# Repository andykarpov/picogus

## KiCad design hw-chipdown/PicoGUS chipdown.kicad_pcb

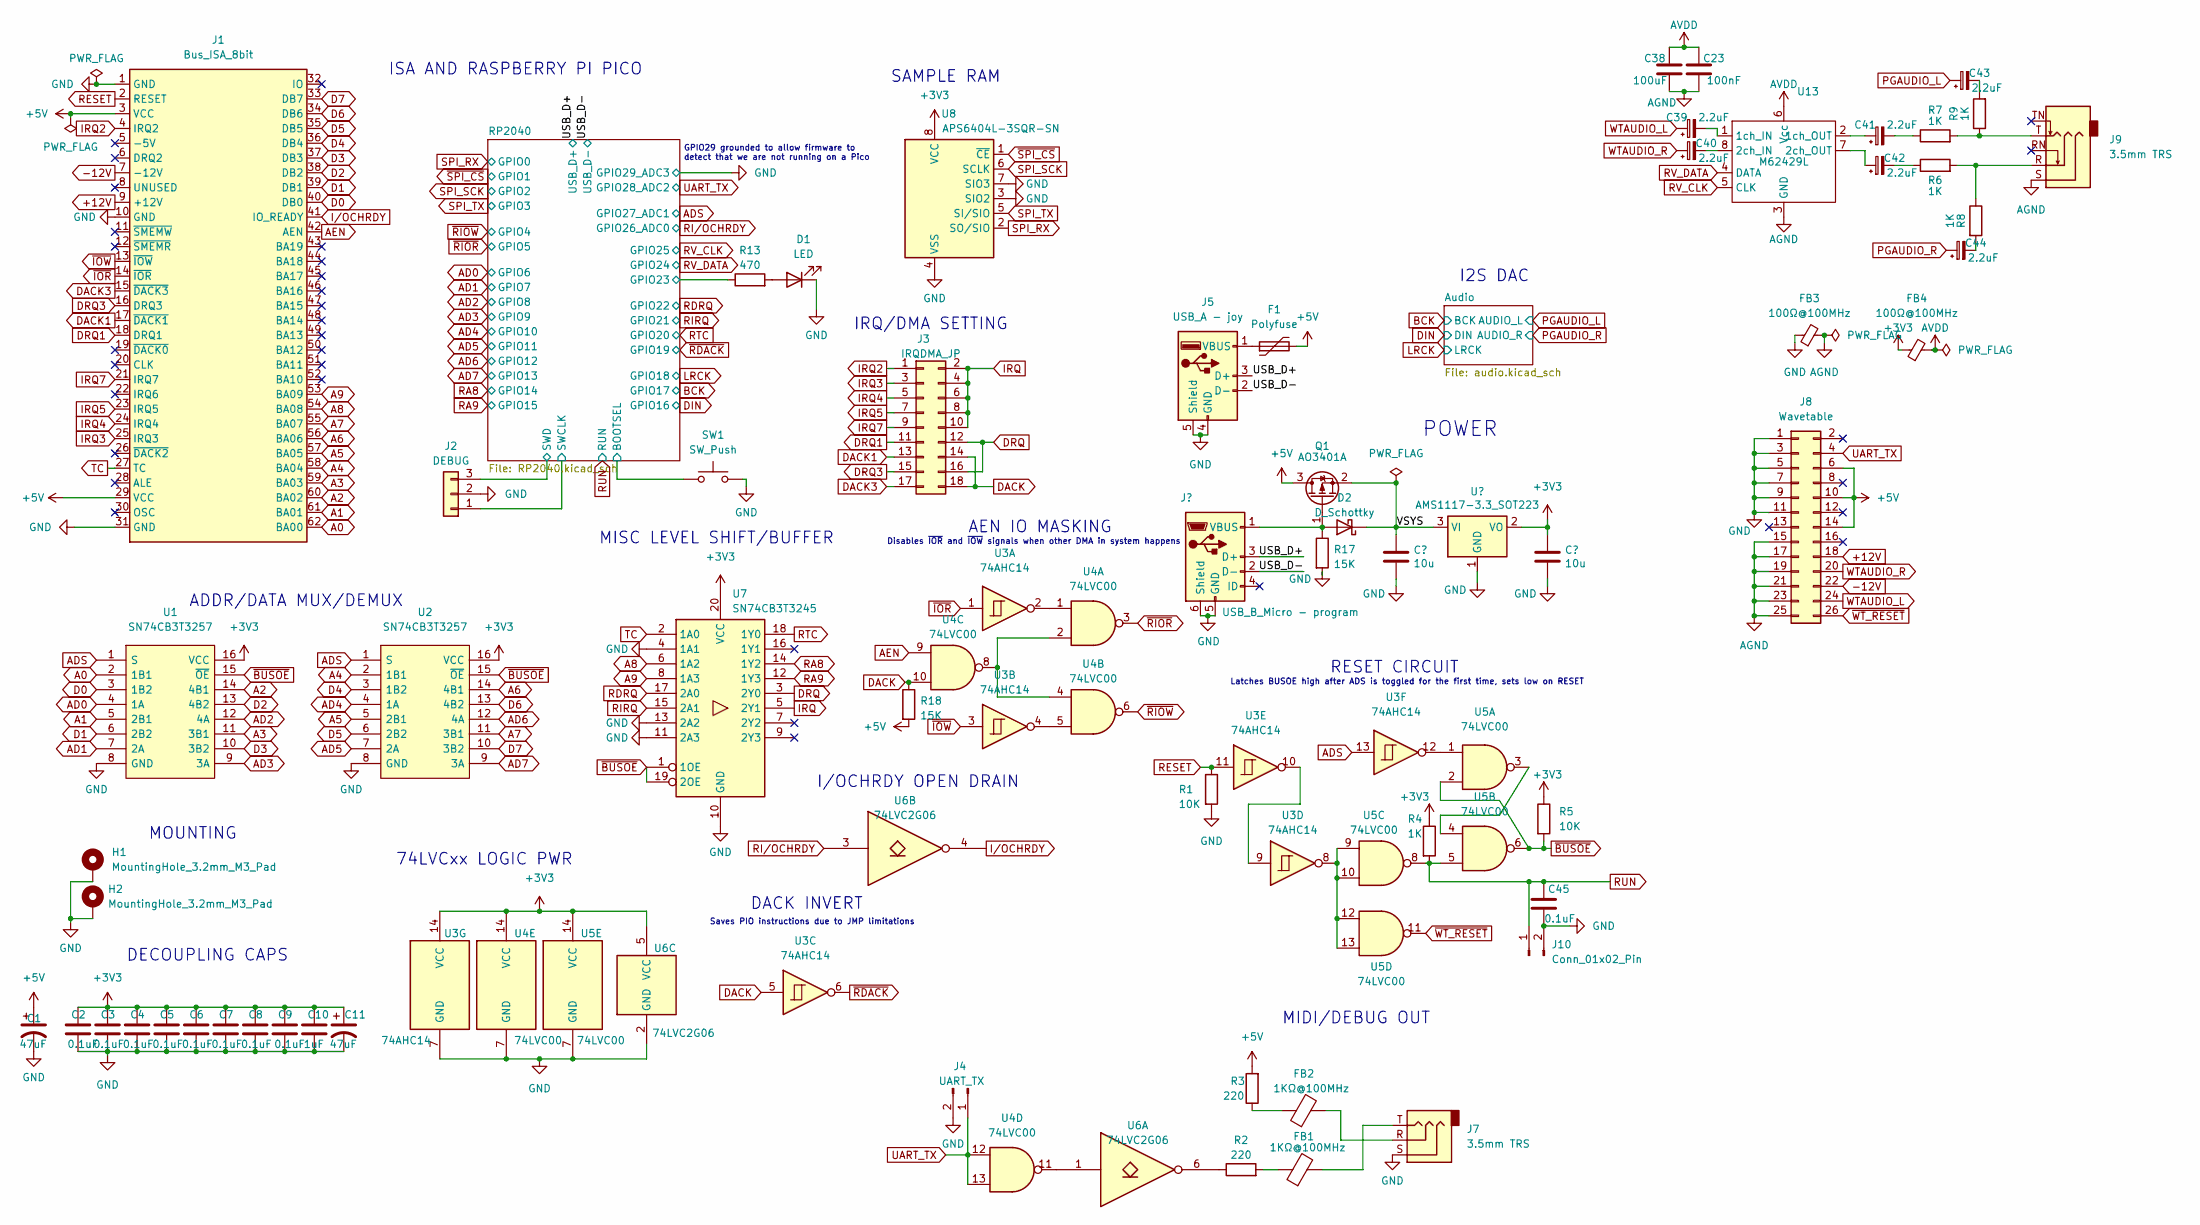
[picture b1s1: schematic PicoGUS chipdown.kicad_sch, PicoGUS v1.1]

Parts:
C1, C11: 47uF; C_1206_3216Metric
C2, C3, C4, C5, C6, C7, C8, C9, C45: 0.1uF; C_0805_2012Metric_Pad1.18x1.45mm_HandSolder
C10: 1uF; C_0805_2012Metric_Pad1.18x1.45mm_HandSolder
C12, C13: 10u; C_0805_2012Metric_Pad1.18x1.45mm_HandSolder
C23: 100nF; C_0805_2012Metric_Pad1.18x1.45mm_HandSolder
C38: 100uF; C_1206_3216Metric
C39, C40, C41, C42, C43, C44: 2.2uF; CP_Elec_4x5.4
D1: LED; LED_0805_2012Metric_Pad1.15x1.40mm_HandSolder
D2: D_Schottky; D_SOD-323_HandSoldering
F1: Polyfuse; Fuse_1206_3216Metric_Pad1.42x1.75mm_HandSolder
FB1, FB2: 1KΩ@100MHz; L_0805_2012Metric_Pad1.15x1.40mm_HandSolder
FB3, FB4: 100Ω@100MHz; L_0805_2012Metric_Pad1.15x1.40mm_HandSolder
H1, H2: MountingHole_3.2mm_M3_Pad
J1: Bus_ISA_8bit; BUS_PC_chamfer
J2: DEBUG; JST_SH_BM03B-SRSS-TB_1x03-1MP_P1.00mm_Vertical
J3: IRQDMA_JP; PinHeader_2x09_P2.54mm_Vertical
J4: UART_TX; PinHeader_1x02_P2.54mm_Vertical
J5: USB_A - joy; USB-A_902-131A1011D10100
J6: USB_B_Micro - program; USB-microB_U254-051T-4BH83-F1S
J7, J9: 3.5mm TRS; Jack_3.5mm_CUI_SJ1-3535NG_Horizontal
J8: Wavetable
J10: Conn_01x02_Pin; PinHeader_1x02_P2.54mm_Vertical
Q1: AO3401A; SOT-23
R1, R5: 10K; R_0805_2012Metric_Pad1.20x1.40mm_HandSolder
R2, R3: 220; R_0805_2012Metric_Pad1.20x1.40mm_HandSolder
R4, R6, R7, R8, R9: 1K; R_0805_2012Metric_Pad1.20x1.40mm_HandSolder
R13: 470; R_0805_2012Metric_Pad1.20x1.40mm_HandSolder
R17, R18: 15K; R_0805_2012Metric_Pad1.20x1.40mm_HandSolder
SW1: SW_Push; SW_SPST_PTS810_handsoldering
U1, U2: SN74CB3T3257; TSSOP-16_4.4x5mm_P0.65mm; Manufacturer_Part_Number 74FST3257DR2G; Mouser Part Number 863-74FST3257DR2G
U3: 74AHC14; TSSOP-14_4.4x5mm_P0.65mm
U4, U5: 74LVC00; TSSOP-14_4.4x5mm_P0.65mm
U6: 74LVC2G06; SOT-363_SC-70-6
U7: SN74CB3T3245; TSSOP-20_4.4x6.5mm_P0.65mm
U8: APS6404L-3SQR-SN; SOIC-8_3.9x4.9mm_P1.27mm
U9: AMS1117-3.3_SOT223; SOT-223-3_TabPin2
U13: M62429L; SOIC-8_3.9x4.9mm_P1.27mm

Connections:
+3V3: C2.1, C3.1, C4.1, C5.1, C6.1, C7.1, C8.1, C9.1, C10.1, C11.1, C13.1, FB4.1, R4.1, R5.1, U1.16 (VCC), U2.16 (VCC), U3.14 (VCC), U4.14 (VCC), U5.14 (VCC), U6.5 (VCC), U7.20 (VCC), U8.8 (VCC), U9.2 (VO); also elsewhere on the board
+5V: C1.1, F1.2, J1.3 (VCC), J1.29 (VCC), J8.6, J8.10, J8.14, Q1.3 (D), R3.2, R18.2
+12V: J1.9 (+12V), J8.18
-12V: J1.7 (-12V), J8.22
/RP2040/GPIO23: R13.1; also elsewhere on the board
/RP2040/SWCLK: J2.1; also elsewhere on the board
/RP2040/SWD: J2.3; also elsewhere on the board
/RP2040/~USB_BOOT: SW1.1; also elsewhere on the board
/USB_D+: J5.3 (D+), J6.3 (D+); also elsewhere on the board
/USB_D-: J5.2 (D-), J6.2 (D-); also elsewhere on the board
/VSYS: C12.1, D2.1 (K), Q1.2 (S), U9.3 (VI)
A0: J1.62 (BA00), U1.2 (1B1)
A1: J1.61 (BA01), U1.5 (2B1)
A2: J1.60 (BA02), U1.14 (4B1)
A3: J1.59 (BA03), U1.11 (3B1)
A4: J1.58 (BA04), U2.2 (1B1)
A5: J1.57 (BA05), U2.5 (2B1)
A6: J1.56 (BA06), U2.14 (4B1)
A7: J1.55 (BA07), U2.11 (3B1)
A8: J1.54 (BA08), U7.6 (1A2)
A9: J1.53 (BA09), U7.8 (1A3)
AD0: U1.4 (1A); also elsewhere on the board
AD1: U1.7 (2A); also elsewhere on the board
AD2: U1.12 (4A); also elsewhere on the board
AD3: U1.9 (3A); also elsewhere on the board
AD4: U2.4 (1A); also elsewhere on the board
AD5: U2.7 (2A); also elsewhere on the board
AD6: U2.12 (4A); also elsewhere on the board
AD7: U2.9 (3A); also elsewhere on the board
ADS: U1.1 (S), U2.1 (S), U3.13; also elsewhere on the board
AEN: J1.42 (AEN), U4.9
AGND: C23.2, C38.2, FB3.2, J8.15, J8.17, J8.19, J8.21, J8.23, J8.25, J9.S, U13.3 (GND); also elsewhere on the board
AVDD: C23.1, C38.1, FB4.2, U13.6 (Vcc); also elsewhere on the board
D0: J1.40 (DB0), U1.3 (1B2)
D1: J1.39 (DB1), U1.6 (2B2)
D2: J1.38 (DB2), U1.13 (4B2)
D3: J1.37 (DB3), U1.10 (3B2)
D4: J1.36 (DB4), U2.3 (1B2)
D5: J1.35 (DB5), U2.6 (2B2)
D6: J1.34 (DB6), U2.13 (4B2)
D7: J1.33 (DB7), U2.10 (3B2)
DACK: J3.14, J3.18, R18.1, U3.5, U4.10
DACK1: J1.17 (~DACK1), J3.13
DACK3: J1.15 (~DACK3), J3.17
DRQ: J3.12, J3.16, U7.3 (2Y0)
DRQ1: J1.18 (DRQ1), J3.11
DRQ3: J1.16 (DRQ3), J3.15
GND: C1.2, C2.2, C3.2, C4.2, C5.2, C6.2, C7.2, C8.2, C9.2, C10.2, C11.2, C12.2, C13.2, C45.2, D1.1 (K), FB3.1, H1.1, H2.1, J1.1 (GND), J1.10 (GND), J1.31 (GND), J2.2, J4.2, J5.4 (GND), J5.5 (Shield), J6.5 (GND), J6.6 (Shield), J7.S, J8.1, J8.3, J8.5, J8.7, J8.9, J8.11, J10.2, R1.2, R17.2, SW1.2, U1.8 (GND), U2.8 (GND), U3.7 (GND), U4.7 (GND), U5.7 (GND), U6.2 (GND), U7.4 (1A1), U7.10 (GND), U7.11 (2A3), U7.13 (2A2), U8.3 (SIO2), U8.4 (VSS), U8.7 (SIO3), U9.1 (GND); also elsewhere on the board
IRQ: J3.2, J3.4, J3.6, J3.8, J3.10, U7.5 (2Y1)
IRQ2: J1.4 (IRQ2), J3.1
IRQ3: J1.25 (IRQ3), J3.3
IRQ4: J1.24 (IRQ4), J3.5
IRQ5: J1.23 (IRQ5), J3.7
IRQ7: J1.21 (IRQ7), J3.9
I/OCHRDY: J1.41 (IO_READY), U6.4
unnamed: C41.2, R7.1
unnamed: C42.2, R6.1
unnamed: C43.2, R9.2
unnamed: C44.2, R8.2
unnamed: D1.2 (A), R13.2
unnamed: D2.2 (A), J6.1 (VBUS), Q1.1 (G), R17.1
unnamed: FB1.1, R2.2
unnamed: FB1.2, J7.T
unnamed: FB2.1, R3.1
unnamed: FB2.2, J7.R
unnamed: F1.1, J5.1 (VBUS)
unnamed: J9.R, R6.2, R8.1
unnamed: J9.T, R7.2, R9.1
unnamed: R2.1, U6.6
unnamed: U3.2, U4.1
unnamed: U3.4, U4.5
unnamed: U3.8, U5.9, U5.10, U5.12, U5.13
unnamed: U3.9, U3.10
unnamed: U3.12, U5.1
unnamed: U4.2, U4.4, U4.8
unnamed: U4.11, U6.1
unnamed: U5.3, U5.4
unnamed: C39.2, U13.1 (1ch_IN)
unnamed: C41.1, U13.2 (1ch_OUT)
unnamed: C40.2, U13.8 (2ch_IN)
unnamed: C42.1, U13.7 (2ch_OUT)
PGAUDIO_L: C43.1; also elsewhere on the board
PGAUDIO_R: C44.1; also elsewhere on the board
RA8: U7.14 (1Y2); also elsewhere on the board
RA9: U7.12 (1Y3); also elsewhere on the board
RDRQ: U7.17 (2A0); also elsewhere on the board
RESET: J1.2 (RESET), R1.1, U3.11
RIRQ: U7.15 (2A1); also elsewhere on the board
RI/OCHRDY: U6.3; also elsewhere on the board
RTC: U7.18 (1Y0); also elsewhere on the board
RUN: C45.1, J10.1, R4.2, U5.5, U5.8; also elsewhere on the board
RV_CLK: U13.5 (CLK); also elsewhere on the board
RV_DATA: U13.4 (DATA); also elsewhere on the board
SPI_RX: U8.2 (SO/SIO); also elsewhere on the board
SPI_SCK: U8.6 (SCLK); also elsewhere on the board
SPI_TX: U8.5 (SI/SIO); also elsewhere on the board
TC: J1.27 (TC), U7.2 (1A0)
UART_TX: J4.1, J8.4, U4.12, U4.13; also elsewhere on the board
WTAUDIO_L: C39.1, J8.24
WTAUDIO_R: C40.1, J8.20
~BUSOE: R5.2, U1.15 (~OE), U2.15 (~OE), U5.2, U5.6, U7.1 (1OE), U7.19 (2OE)
~IOR: J1.14 (~IOR), U3.1
~IOW: J1.13 (~IOW), U3.3
~RDACK: U3.6; also elsewhere on the board
~RIOR: U4.3; also elsewhere on the board
~RIOW: U4.6; also elsewhere on the board
~SPI_CS: U8.1 (~CE); also elsewhere on the board
~WT_RESET: J8.26, U5.11

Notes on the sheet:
Saves PIO instructions due to JMP limitations
DECOUPLING CAPS
GPIO29 grounded to allow firmware to detect that we are not running on a Pico
I2S DAC
Disables ~{IOR} and ~{IOW} signals when other DMA in system happens
Latches BUSOE high after ADS is toggled for the first time, sets low on RESET
MIDI/DEBUG OUT
MOUNTING
MISC LEVEL SHIFT/BUFFER
IRQ/DMA SETTING
DACK INVERT
ADDR/DATA MUX/DEMUX
SAMPLE RAM
AEN IO MASKING
ISA AND RASPBERRY PI PICO
POWER
RESET CIRCUIT
I/OCHRDY OPEN DRAIN
74LVCxx LOGIC PWR

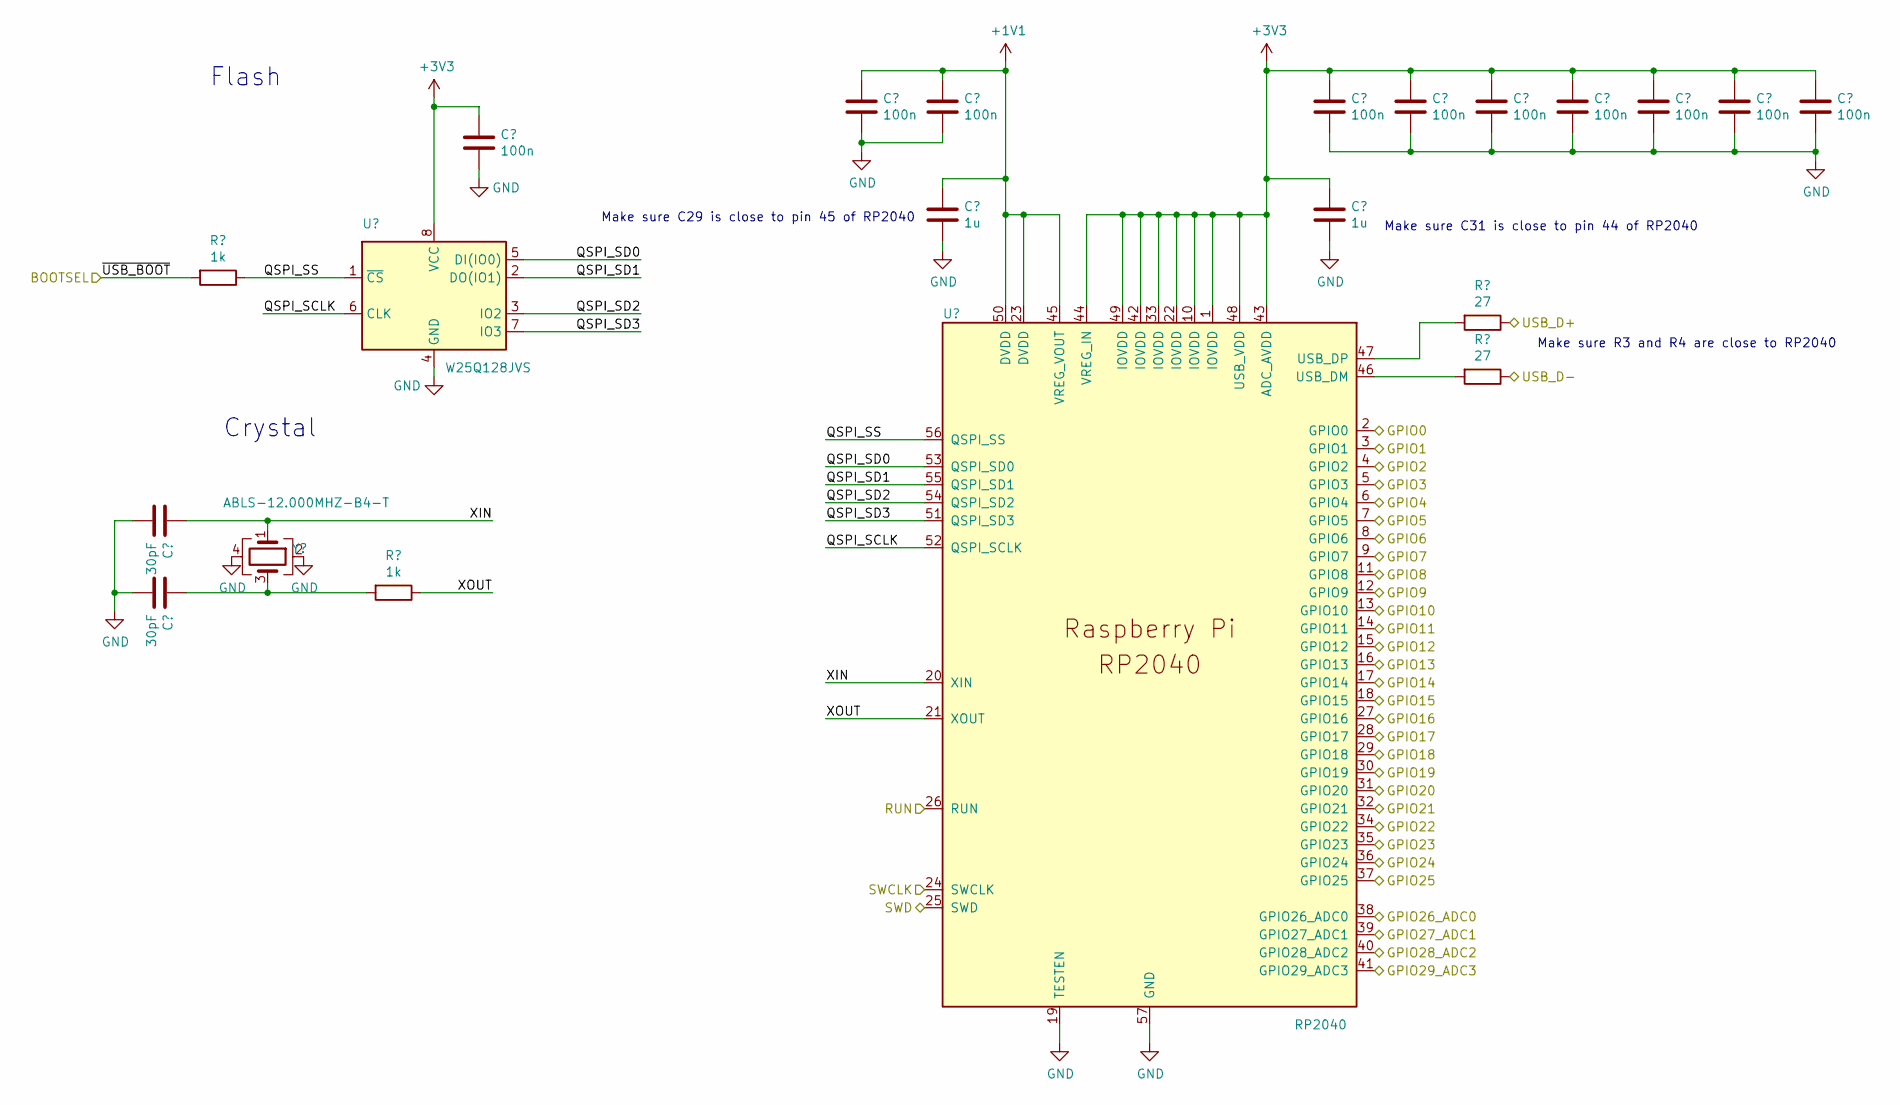
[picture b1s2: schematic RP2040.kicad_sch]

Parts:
C24, C25: 30pF; C_0805_2012Metric_Pad1.18x1.45mm_HandSolder
C26, C27, C28, C30, C32, C33, C34, C35, C36, C37: 100n; C_0805_2012Metric_Pad1.18x1.45mm_HandSolder
C29, C31: 1u; C_0805_2012Metric_Pad1.18x1.45mm_HandSolder
R12, R14: 1k; R_0805_2012Metric_Pad1.20x1.40mm_HandSolder
R15, R16: 27; R_0805_2012Metric_Pad1.20x1.40mm_HandSolder
U11: W25Q128JVS; SOIC-8_5.23x5.23mm_P1.27mm
U12: RP2040; QFN-56-1EP_7x7mm_P0.4mm_EP3.2x3.2mm_ThermalVias
Y1: ABLS-12.000MHZ-B4-T; Crystal_SMD_3225-4Pin_3.2x2.5mm_HandSoldering

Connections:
+1V1: C27.1, C28.1, C29.1, U12.23 (DVDD), U12.45 (VREG_VOUT), U12.50 (DVDD)
+3V3: C26.1, C30.1, C31.1, C32.1, C33.1, C34.1, C35.1, C36.1, C37.1, U11.8 (VCC), U12.1 (IOVDD), U12.10 (IOVDD), U12.22 (IOVDD), U12.33 (IOVDD), U12.42 (IOVDD), U12.43 (ADC_AVDD), U12.44 (VREG_IN), U12.48 (USB_VDD), U12.49 (IOVDD); also elsewhere on the board
/RP2040/GPIO23: U12.35 (GPIO23); also elsewhere on the board
/RP2040/QSPI_SCLK: U11.6 (CLK), U12.52 (QSPI_SCLK)
/RP2040/QSPI_SD0: U11.5 (DI(IO0)), U12.53 (QSPI_SD0)
/RP2040/QSPI_SD1: U11.2 (DO(IO1)), U12.55 (QSPI_SD1)
/RP2040/QSPI_SD2: U11.3 (IO2), U12.54 (QSPI_SD2)
/RP2040/QSPI_SD3: U11.7 (IO3), U12.51 (QSPI_SD3)
/RP2040/QSPI_SS: R12.1, U11.1 (~CS), U12.56 (QSPI_SS)
/RP2040/SWCLK: U12.24 (SWCLK); also elsewhere on the board
/RP2040/SWD: U12.25 (SWD); also elsewhere on the board
/RP2040/XIN: C24.1, U12.20 (XIN), Y1.1
/RP2040/XOUT: R14.1, U12.21 (XOUT)
/RP2040/~USB_BOOT: R12.2; also elsewhere on the board
/USB_D+: R15.1; also elsewhere on the board
/USB_D-: R16.1; also elsewhere on the board
AD0: U12.8 (GPIO6); also elsewhere on the board
AD1: U12.9 (GPIO7); also elsewhere on the board
AD2: U12.11 (GPIO8); also elsewhere on the board
AD3: U12.12 (GPIO9); also elsewhere on the board
AD4: U12.13 (GPIO10); also elsewhere on the board
AD5: U12.14 (GPIO11); also elsewhere on the board
AD6: U12.15 (GPIO12); also elsewhere on the board
AD7: U12.16 (GPIO13); also elsewhere on the board
ADS: U12.39 (GPIO27_ADC1); also elsewhere on the board
BCK: U12.28 (GPIO17); also elsewhere on the board
DIN: U12.27 (GPIO16); also elsewhere on the board
GND: C24.2, C25.2, C26.2, C27.2, C28.2, C29.2, C30.2, C31.2, C32.2, C33.2, C34.2, C35.2, C36.2, C37.2, U11.4 (GND), U12.19 (TESTEN), U12.41 (GPIO29_ADC3), U12.57 (GND), Y1.2, Y1.4; also elsewhere on the board
LRCK: U12.29 (GPIO18); also elsewhere on the board
unnamed: C25.1, R14.2, Y1.3
unnamed: R16.2, U12.46 (USB_DM)
unnamed: R15.2, U12.47 (USB_DP)
RA8: U12.17 (GPIO14); also elsewhere on the board
RA9: U12.18 (GPIO15); also elsewhere on the board
RDRQ: U12.34 (GPIO22); also elsewhere on the board
RIRQ: U12.32 (GPIO21); also elsewhere on the board
RI/OCHRDY: U12.38 (GPIO26_ADC0); also elsewhere on the board
RTC: U12.31 (GPIO20); also elsewhere on the board
RUN: U12.26 (RUN); also elsewhere on the board
RV_CLK: U12.37 (GPIO25); also elsewhere on the board
RV_DATA: U12.36 (GPIO24); also elsewhere on the board
SPI_RX: U12.2 (GPIO0); also elsewhere on the board
SPI_SCK: U12.4 (GPIO2); also elsewhere on the board
SPI_TX: U12.5 (GPIO3); also elsewhere on the board
UART_TX: U12.40 (GPIO28_ADC2); also elsewhere on the board
~RDACK: U12.30 (GPIO19); also elsewhere on the board
~RIOR: U12.7 (GPIO5); also elsewhere on the board
~RIOW: U12.6 (GPIO4); also elsewhere on the board
~SPI_CS: U12.3 (GPIO1); also elsewhere on the board

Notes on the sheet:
Make sure R3 and R4 are close to RP2040
Make sure C29 is close to pin 45 of RP2040
Make sure C31 is close to pin 44 of RP2040
Flash
Crystal

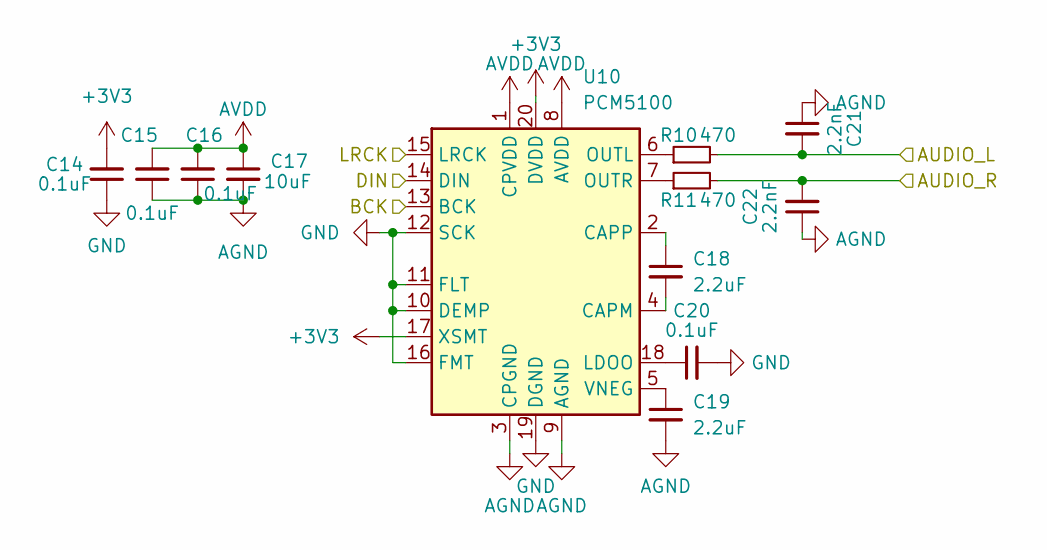
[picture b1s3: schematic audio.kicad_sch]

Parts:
C14, C15, C16, C20: 0.1uF; C_0805_2012Metric_Pad1.18x1.45mm_HandSolder
C17: 10uF; C_0805_2012Metric_Pad1.18x1.45mm_HandSolder
C18, C19: 2.2uF; C_0805_2012Metric_Pad1.18x1.45mm_HandSolder
C21, C22: 2.2nF; C_0805_2012Metric_Pad1.18x1.45mm_HandSolder
R10, R11: 470; R_0805_2012Metric_Pad1.20x1.40mm_HandSolder
U10: PCM5100; TSSOP-20_4.4x6.5mm_P0.65mm

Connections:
+3V3: C14.2, U10.17 (XSMT), U10.20 (DVDD); also elsewhere on the board
AGND: C15.1, C16.1, C17.2, C19.2, C21.1, C22.1, U10.3 (CPGND), U10.9 (AGND); also elsewhere on the board
AVDD: C15.2, C16.2, C17.1, U10.1 (CPVDD), U10.8 (AVDD); also elsewhere on the board
BCK: U10.13 (BCK); also elsewhere on the board
DIN: U10.14 (DIN); also elsewhere on the board
GND: C14.1, C20.2, U10.10 (DEMP), U10.11 (FLT), U10.12 (SCK), U10.16 (FMT), U10.19 (DGND); also elsewhere on the board
LRCK: U10.15 (LRCK); also elsewhere on the board
unnamed: C18.2, U10.4 (CAPM)
unnamed: C18.1, U10.2 (CAPP)
unnamed: C20.1, U10.18 (LDOO)
unnamed: R10.1, U10.6 (OUTL)
unnamed: R11.1, U10.7 (OUTR)
unnamed: C19.1, U10.5 (VNEG)
PGAUDIO_L: C21.2, R10.2; also elsewhere on the board
PGAUDIO_R: C22.2, R11.2; also elsewhere on the board

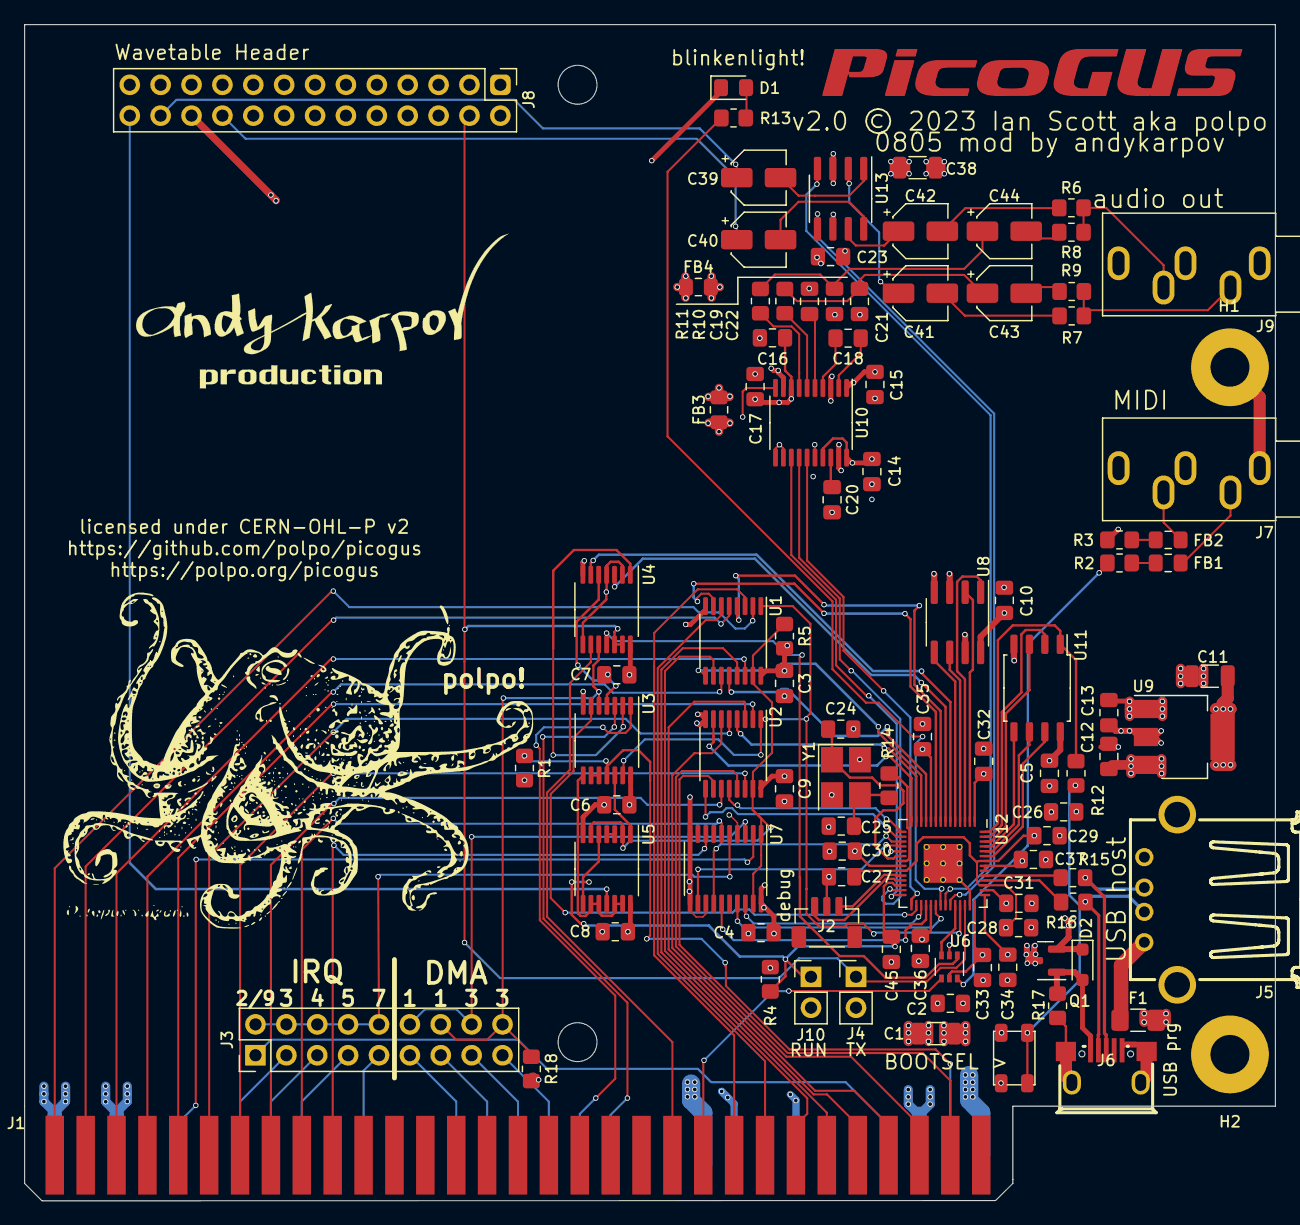
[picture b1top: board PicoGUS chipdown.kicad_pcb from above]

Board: 4 copper layers, 102.9 x 96.7 mm, 98 parts (0 on the bottom side), 129 nets.

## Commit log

2025-01-15 v2.0 with 0805 components
2025-01-15 Gerbers and ibom for 0805 chipdown version

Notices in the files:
hw-chipdown/PicoGUS chipdown.kicad_pcb:
licensed under CERN-OHL-P v2
v2.0 © 2023 Ian Scott aka polpo
